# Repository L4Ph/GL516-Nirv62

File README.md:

<!--最初にロゴ・アイキャッチ画像などを表示
KLEのレイアウト画像とロゴなんかがよさそう-->

[Keyboard Layout Editor Permalink](http://www.keyboard-layout-editor.com/##@@_x:1&a:7%3B&=SW1&=SW6&=SW10&=SW14&=SW18&=SW23&=SW28&_x:0.5%3B&=SW34&=SW38&=SW43&=SW48&_w:2%3B&=SW53%3B&@_x:0.75&w:1.5%3B&=SW2&=SW7&=SW11&=SW15&=SW19&=SW24&=SW29&=SW35&=SW39&=SW44&=SW49&=SW54&=SW57&_w:1.5%3B&=SW60%3B&@_x:0.25&w:1.75%3B&=SW3&=SW8&=SW12&=SW16&=SW20&=SW25&=SW30&_x:0.5%3B&=SW36&=SW40&=SW45&=SW50&=SW55&_w:2.25%3B&=SW58%3B&@_w:1.75%3B&=SW4&=SW9&=SW13&=SW17&=SW21&=SW26&=SW31&=SW33&=SW37&=SW41&=SW46&=SW51&_a:4%3B&=%0A.%0A%0A%0A%0A%0A%0A%0A%0ASW56&_a:7%3B&=SW59&=SW61%3B&@_w:1.25%3B&=SW5&_x:1&w:1.25%3B&=SW22&_w:2.75%3B&=SW27&_w:1.25%3B&=SW32&_x:1.5%3B&=SW42&_w:2.25%3B&=SW47&_w:1.25%3B&=SW52&_x:1&w:1.25%3B&=SW62)

# Nirv62

<!--imgurかGyazoがいいと思います-->

## 販売先
[遊舎工房](https://shop.yushakobo.jp)　

[BOOTH](https://booth.pm)

## 特徴や概要
1. 
2.
3.

## ビルドガイド等
[共通ビルドガイド](https://github.com/L4Ph/GL516_BuildGuide)

## キーキャップ

| サイズ | 個数 | 備考 |
| :----: | :---- | :----: |
| セット参考 | n | [Simple Purple Dye-Subbed Keycap Set](https://shop.yushakobo.jp/collections/keycaps-1/products/2775) |
| 1U | n | a |
|  1.25U | n | b |
| 1.5U | n | c |
| 1.75U | n | d |
| 2U | n | e |
| 2.25U | n | f |
| 2.75U | n | g |

## 注意事項
<!--注意点などがあれば書く-->

## 文責
<!--作成情報を列挙-->
* 作成者/[@twitter_username](https://twitter.com/)
* 連絡先/
* サポート先等/

## ライセンス
<!--ライセンスを明示する-->

"GL516_" is under [MIT license](https://en.wikipedia.org/wiki/MIT_License).

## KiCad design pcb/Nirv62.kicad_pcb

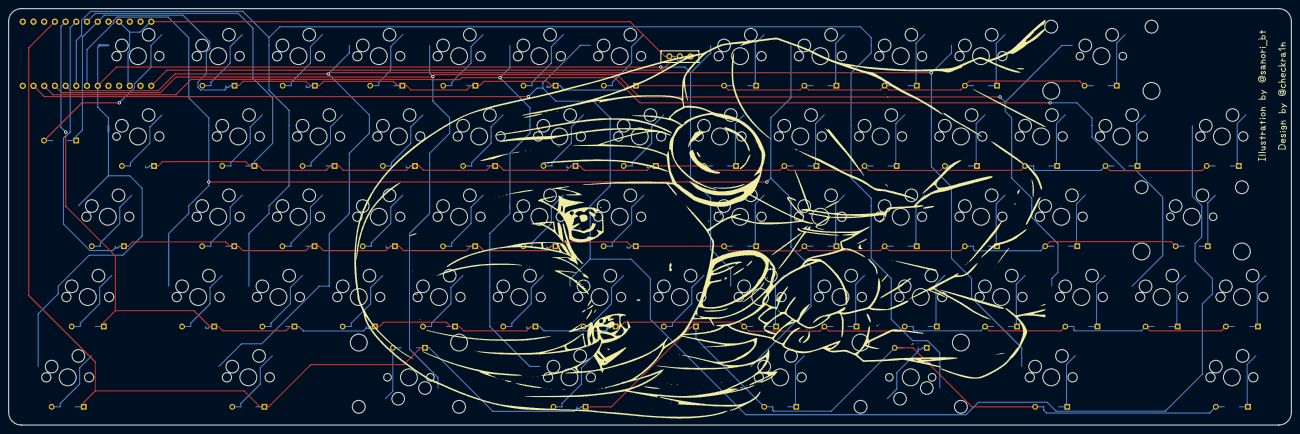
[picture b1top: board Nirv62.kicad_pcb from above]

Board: 2 copper layers, 304.4 x 98.8 mm, 128 parts (1 on the bottom side), 76 nets.

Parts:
D1, D2, D3, D4, D5, D6, D7, D8, D9, D10, D11, D12, D13, D14, D15, D16, D17, D18, D19, D20, D21, D22, D23, D24, D25, D26, D27, D28, D29, D30, D31, D32, D33, D34, D35, D36, D37, D38, D39, D40, D41, D42, D43, D44, D45, D46, D47, D48, D49, D50, D51, D52, D53, D54, D55, D56, D57, D58, D59, D60, D61, D62: D; Diode_TH_SMD
J1: Conn_01x02; Battery_XH2.5_GL_PCB
SW1, SW6, SW7, SW8, SW9, SW10, SW11, SW12, SW13, SW14, SW15, SW16, SW17, SW18, SW19, SW20, SW21, SW23, SW24, SW25, SW26, SW28, SW29, SW30, SW31, SW33, SW34, SW35, SW36, SW37, SW38, SW39, SW40, SW41, SW42, SW43, SW44, SW45, SW46, SW48, SW49, SW50, SW51, SW54, SW55, SW56, SW57, SW59, SW60, SW61: SW_PUSH; CherryMX_Hotswap_1.0u
SW2: SW_PUSH; CherryMX_Hotswap_1.5u
SW3, SW4: SW_PUSH; CherryMX_Hotswap_1.75u
SW5, SW22, SW32, SW52, SW62: SW_PUSH; CherryMX_Hotswap_1.25u
SW27: SW_PUSH; CherryMX_Hotswap_2.75u
SW47, SW58: SW_PUSH; CherryMX_Hotswap_2.25u
SW53: SW_PUSH; CherryMX_Hotswap_2u
U1: BLEMicroPro; Micon_BMP_GL
designer_logo: LOGO; pcb_desinger
sanori_logo: LOGO; sanori_logo

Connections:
Bat+: J1.1, U1.25
Col0: SW1.1, SW2.1, SW3.1, SW4.1, SW5.1, SW34.1, SW35.1, SW36.1, SW37.1, U1.20
Col1: SW6.1, SW7.1, SW8.1, SW9.1, SW38.1, SW39.1, SW40.1, SW41.1, SW42.1, U1.19
Col2: SW10.1, SW11.1, SW12.1, SW13.1, SW43.1, SW44.1, SW45.1, SW46.1, SW47.1, U1.18
Col3: SW14.1, SW15.1, SW16.1, SW17.1, SW22.1, SW48.1, SW49.1, SW50.1, SW51.1, SW52.1, U1.17
Col4: SW18.1, SW19.1, SW20.1, SW21.1, SW27.1, SW53.1, SW54.1, SW55.1, SW56.1, U1.16
Col5: SW23.1, SW24.1, SW25.1, SW26.1, SW32.1, SW57.1, SW58.1, SW59.1, U1.15
Col6: SW28.1, SW29.1, SW30.1, SW31.1, SW33.1, SW60.1, SW61.1, SW62.1, U1.14
GND: J1.2, U1.3, U1.4, U1.23, U1.26
unnamed: D1.2, SW1.2
unnamed: D2.2, SW2.2
unnamed: D3.2, SW3.2
unnamed: D4.2, SW4.2
unnamed: D5.2, SW5.2
unnamed: D6.2, SW6.2
unnamed: D7.2, SW7.2
unnamed: D8.2, SW8.2
unnamed: D9.2, SW9.2
unnamed: D10.2, SW10.2
unnamed: D11.2, SW11.2
unnamed: D12.2, SW12.2
unnamed: D13.2, SW13.2
unnamed: D14.2, SW14.2
unnamed: D15.2, SW15.2
unnamed: D16.2, SW16.2
unnamed: D17.2, SW17.2
unnamed: D18.2, SW18.2
unnamed: D19.2, SW19.2
unnamed: D20.2, SW20.2
unnamed: D21.2, SW21.2
unnamed: D22.2, SW22.2
unnamed: D23.2, SW23.2
unnamed: D24.2, SW24.2
unnamed: D25.2, SW25.2
unnamed: D26.2, SW26.2
unnamed: D27.2, SW27.2
unnamed: D28.2, SW28.2
unnamed: D29.2, SW29.2
unnamed: D30.2, SW30.2
unnamed: D31.2, SW31.2
unnamed: D32.2, SW32.2
unnamed: D33.2, SW33.2
unnamed: D34.1, SW34.2
unnamed: D35.1, SW35.2
unnamed: D36.1, SW36.2
unnamed: D37.1, SW37.2
unnamed: D38.1, SW38.2
unnamed: D39.1, SW39.2
unnamed: D40.1, SW40.2
unnamed: D41.1, SW41.2
unnamed: D42.1, SW42.2
unnamed: D43.1, SW43.2
unnamed: D44.1, SW44.2
unnamed: D45.1, SW45.2
unnamed: D46.1, SW46.2
unnamed: D47.1, SW47.2
unnamed: D48.1, SW48.2
unnamed: D49.1, SW49.2
unnamed: D50.1, SW50.2
unnamed: D51.1, SW51.2
unnamed: D52.1, SW52.2
unnamed: D53.1, SW53.2
unnamed: D54.1, SW54.2
unnamed: D55.1, SW55.2
unnamed: D56.1, SW56.2
unnamed: D57.1, SW57.2
unnamed: D58.1, SW58.2
unnamed: D59.1, SW59.2
unnamed: D60.1, SW60.2
unnamed: D61.1, SW61.2
unnamed: D62.1, SW62.2
Row0: D1.1, D6.1, D10.1, D14.1, D18.1, D23.1, D28.1, D34.2, D38.2, D43.2, D48.2, D53.2, U1.5
Row1: D2.1, D7.1, D11.1, D15.1, D19.1, D24.1, D29.1, D35.2, D39.2, D44.2, D49.2, D54.2, D57.2, D60.2, U1.6
Row2: D3.1, D8.1, D12.1, D16.1, D20.1, D25.1, D30.1, D36.2, D40.2, D45.2, D50.2, D55.2, D58.2, U1.7
Row3: D4.1, D9.1, D13.1, D17.1, D21.1, D26.1, D31.1, D37.2, D41.2, D46.2, D51.2, D56.2, D59.2, D61.2, U1.8
Row4: D5.1, D22.1, D27.1, D32.1, D33.1, D42.2, D47.2, D52.2, D62.2, U1.9

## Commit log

2021-09-09 add files
